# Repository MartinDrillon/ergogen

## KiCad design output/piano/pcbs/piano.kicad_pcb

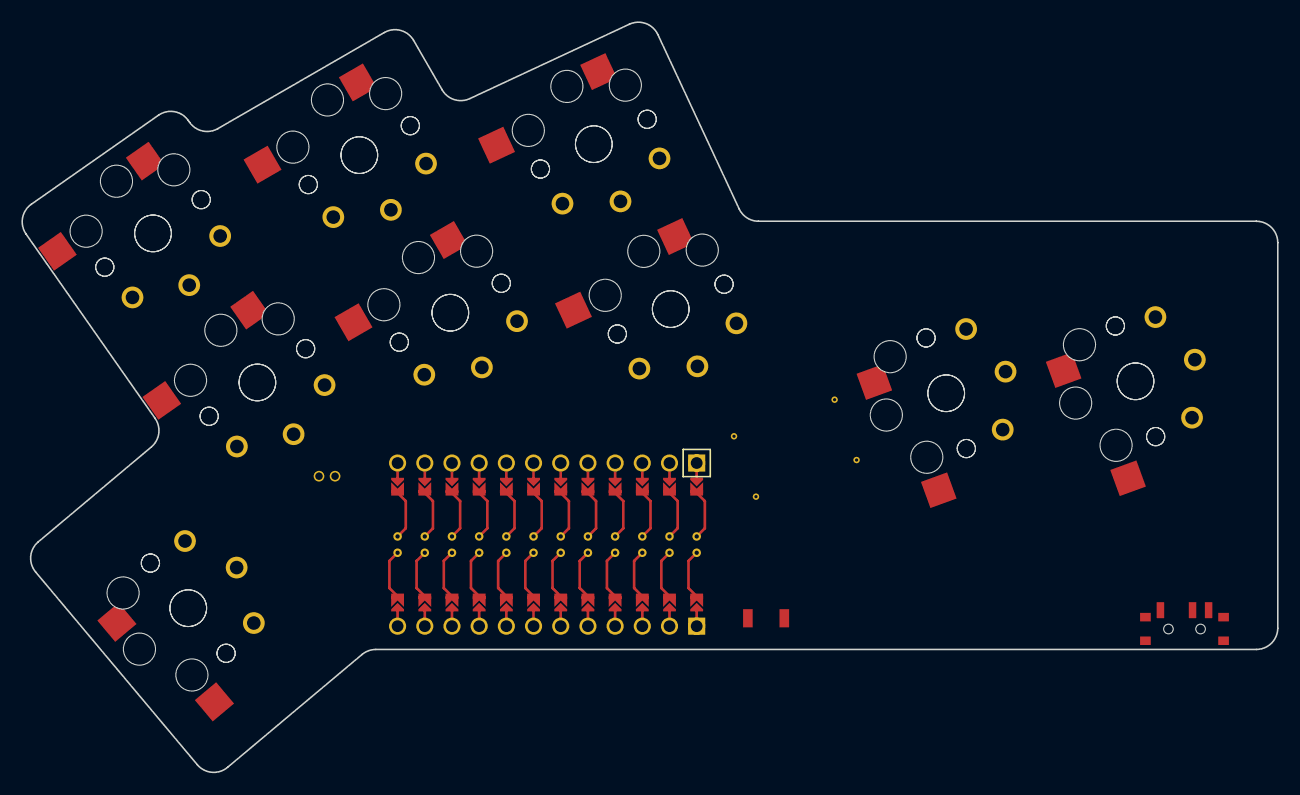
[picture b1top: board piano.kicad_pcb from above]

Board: 2 copper layers, 117.3 x 70.1 mm, 19 parts (0 on the bottom side), 10 nets, no tracks yet.

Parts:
MCU1: ProMicro
S1, S2, S3, S4, S5, S6, S7, S8, S9, S10, S11, S12, S13, S14, S15, S16, S17, S18: PG1350

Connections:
GND: MCU1.2, MCU1.21, MCU1.22, S1.2, S2.2, S3.2, S4.2, S5.2, S6.2, S7.2, S8.2, S9.2, S10.2, S11.2, S12.2, S13.2, S14.2, S15.2, S16.2, S17.2, S18.2
P0: MCU1.23, S15.1, S16.1
P1: MCU1.24, S17.1, S18.1
P4: MCU1.18, S11.1, S12.1
P5: MCU1.17, S13.1, S14.1
P8: MCU1.14, S5.1, S6.1
P9: MCU1.13, S3.1, S4.1
P10: MCU1.12, S1.1, S2.1
P14: MCU1.10, S9.1, S10.1
P15: MCU1.9, S7.1, S8.1

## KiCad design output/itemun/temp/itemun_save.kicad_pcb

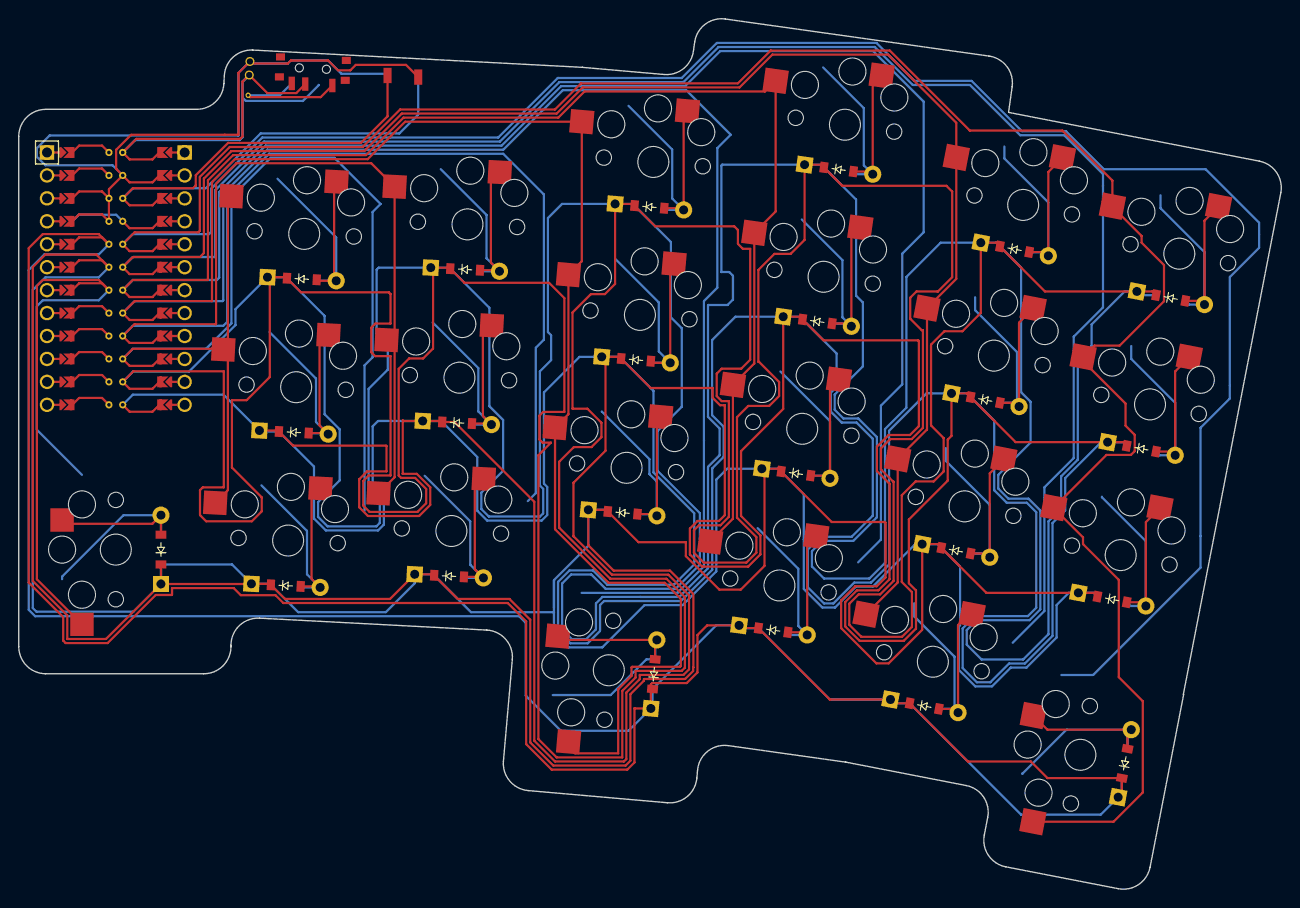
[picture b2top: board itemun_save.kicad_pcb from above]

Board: 2 copper layers, 139.8 x 96.4 mm, 47 parts (0 on the bottom side), 35 nets.

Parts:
D1, D2, D3, D4, D5, D6, D7, D8, D9, D10, D11, D12, D13, D14, D15, D16, D17, D18, D19, D20, D21, D22, D23: ComboDiode
MCU1: ProMicro
S1, S2, S3, S4, S5, S6, S7, S8, S9, S10, S11, S12, S13, S14, S15, S16, S17, S18, S19, S20, S21, S22, S23: PG1350

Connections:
GND: MCU1.2, MCU1.21, MCU1.22
P2: D20.1, D20.2, D21.1, D21.2, D22.1, D22.2, D23.1, D23.2, MCU1.20
P3: D1.1, D1.2, D2.1, D2.2, D5.1, D5.2, D8.1, D8.2, D11.1, D11.2, D14.1, D14.2, D17.1, D17.2, MCU1.19
P4: MCU1.18, S1.2
P10: D3.1, D3.2, D6.1, D6.2, D9.1, D9.2, D12.1, D12.2, D15.1, D15.2, D18.1, D18.2, MCU1.12
P14: MCU1.10, S2.2, S3.2, S4.2
P15: MCU1.9, S5.2, S6.2, S7.2
P16: D4.1, D4.2, D7.1, D7.2, D10.1, D10.2, D13.1, D13.2, D16.1, D16.2, D19.1, D19.2, MCU1.11
P18: MCU1.8, S8.2, S9.2, S10.2, S20.2
P19: MCU1.7, S11.2, S12.2, S13.2, S21.2
P20: MCU1.6, S14.2, S15.2, S16.2, S22.2
P21: MCU1.5, S17.2, S18.2, S19.2, S23.2
alt_first: D21.1, D21.2, S21.1
ctrl_first: D20.1, D20.2, S20.1
e_first: D23.1, D23.2, S23.1
index_bottom: D14.1, D14.2, S14.1
index_home: D15.1, D15.2, S15.1
index_top: D16.1, D16.2, S16.1
inner_bottom: D17.1, D17.2, S17.1
inner_home: D18.1, D18.2, S18.1
inner_top: D19.1, D19.2, S19.1
middle_bottom: D11.1, D11.2, S11.1
middle_home: D12.1, D12.2, S12.1
middle_top: D13.1, D13.2, S13.1
outer_bottom: D2.1, D2.2, S2.1
outer_home: D3.1, D3.2, S3.1
outer_top: D4.1, D4.2, S4.1
outouter_bottom: D1.1, D1.2, S1.1
pinkie_bottom: D5.1, D5.2, S5.1
pinkie_home: D6.1, D6.2, S6.1
pinkie_top: D7.1, D7.2, S7.1
ring_bottom: D8.1, D8.2, S8.1
ring_home: D9.1, D9.2, S9.1
ring_top: D10.1, D10.2, S10.1
shift_first: D22.1, D22.2, S22.1
